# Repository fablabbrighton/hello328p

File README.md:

# Hello 328p!

**Hello 328p** is designed to be a 100% Arduino Uno-compatible board, that can be easily fabricated by students in a fablab. It uses the ATmega328P microcontroller and is very heavily based on [Daniele Ingrassia's Satshakit board](https://github.com/satshakit/satshakit), which also serves the same purpose. The main changes to this design are to provide a simpler way to connect things to the board through more convenient headers and labelling on the board itself.

Please read [Daniele's documentation](https://github.com/satshakit/satshakit) for full details on this board. These docs will only address the changes made.

## Background

I have spent a few months exploring different approaches to making your own Arduino-compatible board. My aim is to find (or design myself) a board that can be easily milled and stuffed by students, and then used in their own interactive projects. I also wanted to lern more about Arduino, the ATMega328p and board design in the process. 

You can read more about that here: [DIY Arduino docs](https://fablabbrighton.github.io/digital-fabrication-module/diy-arduino/)

After trying many boards is a starting point, I found Daniele's Satshakit design, which was well-documented, simple, and tested in a Fablab. I successfully made and programmed the board, but I found the header arrangement rather unhelpful.

In this photo, I'm using my FabISP to program a Satshakit. You can see that it involves a lot of jumper wires, and that there is no simple connection between the 3x2 pin ISP header on the programmer, and the relevant pins on the target board. 

Similarly, programming using an FTDI cable or breakout board (as in the photo above) involves a non-intuitive routing of pins from the programming cable (or board) to the target.

The upside of this approach is that the board design is very simple. Almost all the pins from the microcontroller are simply exposed out to pins on headers that surround it. The traces are very straightforward.

However, that pushes some complexity back onto the user, who has to figure out which pins to connect where, when burning the bootloader, or whenever they want to program the board. I think there is a friendlier way to do this, with only a small overhead in complexity of traces. _Hello 328p_ is my attempt at that.

The photo below shows the Hello 328p board being programmed with a FabISP, via one simple ribbon cable. You can also see the handy pads for connecting a power supply with crocodile clips.

## Hello 328p header layout

This diagram shows all the headers, and which pins on the chip they are connected to. In addition, pin functions for the FTDI and ISP headers are highlighted in pink, and the Arduino labels for analogue and digital pins are highlighted in yellow.

You may also wish to consult the official pinout for the ATmega328P chip (TQFP package) from the datasheet:

## Programming the board

Following the Satshakit instructions: 

> A satshakit board is **totally like an Arduino board**, thus is possible to use the Arduino IDE without any modification. When you finish solder satshakit, you're ready to program it. If you want to use satshakit as an Arduino, you first need to **upload Arduino bootloader**. This will also set the ATmega328P fuses as the same of an Arduino UNO.
> To do this you need to use a **programmer**, for example another Arduino or FabISP. If you plan to program a satshakit with an Arduino, be sure to upload the **Arduino as ISP skecth** before connecting the satshakit to it.

Where we diverge from the Satshakit process is that our connections are simpler. If you're using a FabISP, simply connect the ribbon cable to the ISP on both boards. the GND pin on the ISP heder is marked with a G.

To program with an FTDI cable, simply connect to the header labelled FTDI. Again, the GND pin is marked with a G.

Returning to the original instructions:

> Once everything is connected, follow these steps to upload Arduino bootloader:

> 1. open Arduino IDE
> 2. select proper programmer (for example Arduino as ISP or USBtinyISP)
> 3. select Arduino UNO as board
> 4. click on tools->Burn Bootloader

> With a satshakit cnc or satshakit laser you can use an **FTDI USB cable to upload and use you favourite sketch** without the need to use a programmer anymore.

> Remember that if you don't have an FTDI cable you always need a programmer, and to select **File->Upload using a programmer** to upload the code to satshakit.

License
--
This work is licensed under the terms of Attribution-NonCommercial-ShareAlike 4.0 International ([CC BY-NC-SA 4.0](https://creativecommons.org/licenses/by-nc-sa/4.0/)).

Disclaimer  
--

<div class="align-justify">
This hardware/software is provided "as is", and you use the hardware/software at your own risk. Under no circumstances shall any author be liable for direct, indirect, special, incidental, or consequential damages resulting from the use, misuse, or inability to use this hardware/software, even if the authors have been advised of the possibility of such damages.</div>

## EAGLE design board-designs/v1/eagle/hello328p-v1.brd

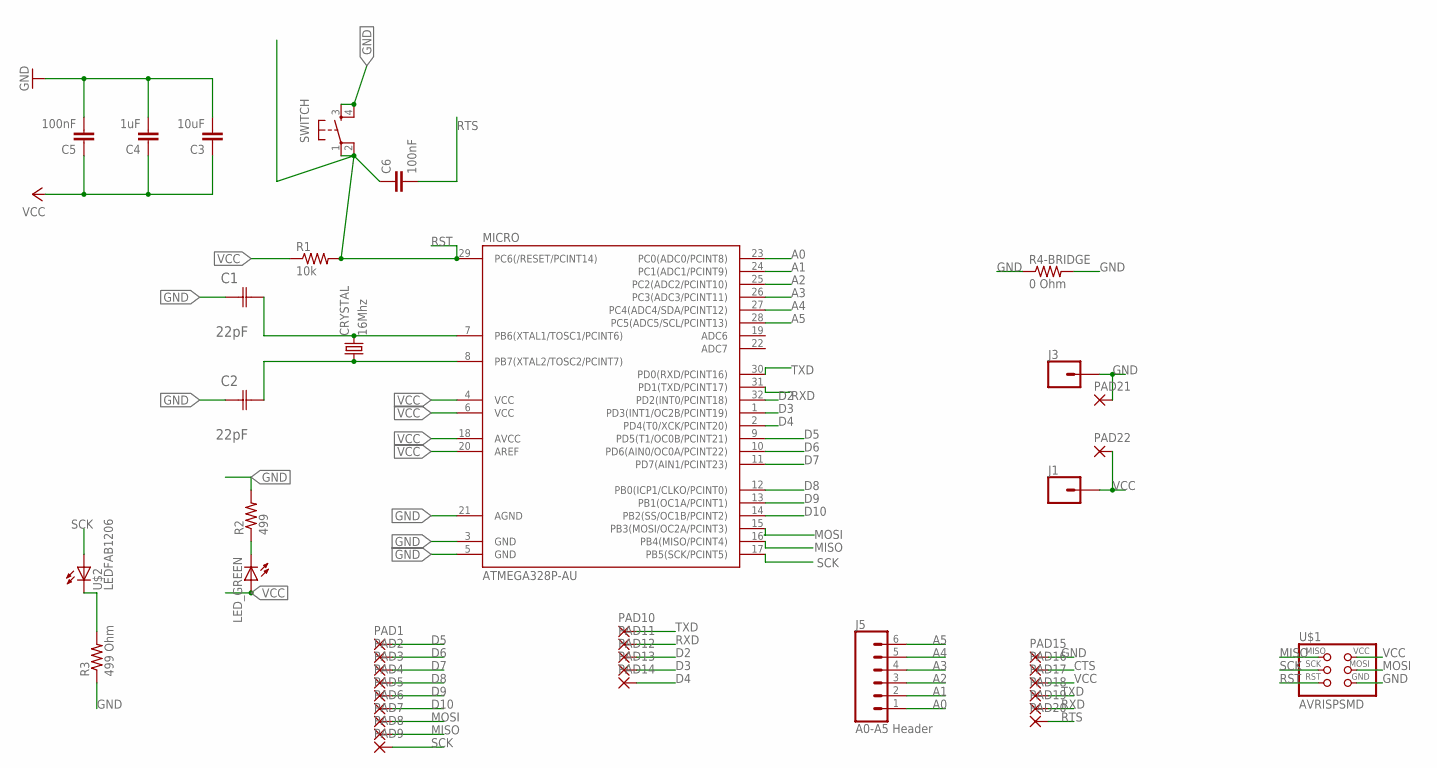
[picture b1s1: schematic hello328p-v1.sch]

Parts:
C1, C2: 22pF; CAPC3216X178N
C3: 10uF; 1206
C4: 1uF; 1206
C5, C6: 100nF; 1206
CRYSTAL: 16Mhz; CSM-7X-DU
J1, J3: CONN_01SNAP-MALE; SNAP-MALE
J5: A0-A5 Header; 1X06_SMD_MALE
LED_GREEN: LED1206; 1206
MICRO: ATMEGA328P-AU; TQFP32-08
PAD1, PAD2, PAD3, PAD4, PAD5, PAD6, PAD7, PAD8, PAD9, PAD10, PAD11, PAD12, PAD13, PAD14, PAD15, PAD16, PAD17, PAD18, PAD19, PAD20, PAD21, PAD22: SMD2; SMD1,27-2,54
R1: 10k; 1206
R2: 499; 1206
R3: 499 Ohm; R1206FAB
R4-BRIDGE: 0 Ohm; R1206FAB
SWITCH: 6MM_SWITCH6MM_SWITCH; 6MM_SWITCH
U$1: AVRISPSMD; 2X03SMD
U$2: LEDFAB1206; LED1206FAB

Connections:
A0: J5.1, MICRO.23 (PC0(ADC0/PCINT8))
A1: J5.2, MICRO.24 (PC1(ADC1/PCINT9))
A2: J5.3, MICRO.25 (PC2(ADC2/PCINT10))
A3: J5.4, MICRO.26 (PC3(ADC3/PCINT11))
A4: J5.5, MICRO.27 (PC4(ADC4/SDA/PCINT12))
A5: J5.6, MICRO.28 (PC5(ADC5/SCL/PCINT13))
CTS: PAD16.1
D2: MICRO.32 (PD2(INT0/PCINT18)), PAD12.1
D3: MICRO.1 (PD3(INT1/OC2B/PCINT19)), PAD13.1
D4: MICRO.2 (PD4(T0/XCK/PCINT20)), PAD14.1
D5: MICRO.9 (PD5(T1/OC0B/PCINT21)), PAD1.1
D6: MICRO.10 (PD6(AIN0/OC0A/PCINT22)), PAD2.1
D7: MICRO.11 (PD7(AIN1/PCINT23)), PAD3.1
D8: MICRO.12 (PB0(ICP1/CLKO/PCINT0)), PAD4.1
D9: MICRO.13 (PB1(OC1A/PCINT1)), PAD5.1
D10: MICRO.14 (PB2(SS/OC1B/PCINT2)), PAD6.1
GND: C1.1 (C1), C2.1 (C1), C3.2, C4.2, C5.2, J3.2, MICRO.3 (GND), MICRO.5 (GND), MICRO.21 (AGND), PAD15.1, PAD21.1, R2.2, R3.1, R4-BRIDGE.1, R4-BRIDGE.2, SWITCH.3 (S), SWITCH.4 (S1), U$1.6 (GND)
MISO: MICRO.16 (PB4(MISO/PCINT4)), PAD8.1, U$1.1 (MISO)
MOSI: MICRO.15 (PB3(MOSI/OC2A/PCINT3)), PAD7.1, U$1.4 (MOSI)
unnamed: R3.2, U$2.2 (C)
unnamed: C1.2 (C2), CRYSTAL.2, MICRO.7 (PB6(XTAL1/TOSC1/PCINT6))
unnamed: C2.2 (C2), CRYSTAL.1, MICRO.8 (PB7(XTAL2/TOSC2/PCINT7))
unnamed: LED_GREEN.2 (C), R2.1
RST: C6.1, MICRO.29 (PC6(/RESET/PCINT14)), R1.2, SWITCH.1, SWITCH.2 (P1), U$1.5 (RST)
RTS: C6.2, PAD20.1
RXD: MICRO.31 (PD1(TXD/PCINT17)), PAD11.1, PAD19.1
SCK: MICRO.17 (PB5(SCK/PCINT5)), PAD9.1, U$1.3 (SCK), U$2.1 (A)
TXD: MICRO.30 (PD0(RXD/PCINT16)), PAD10.1, PAD18.1
VCC: C3.1, C4.1, C5.1, J1.2, LED_GREEN.1 (A), MICRO.4 (VCC), MICRO.6 (VCC), MICRO.18 (AVCC), MICRO.20 (AREF), PAD17.1, PAD22.1, R1.1, U$1.2 (VCC)

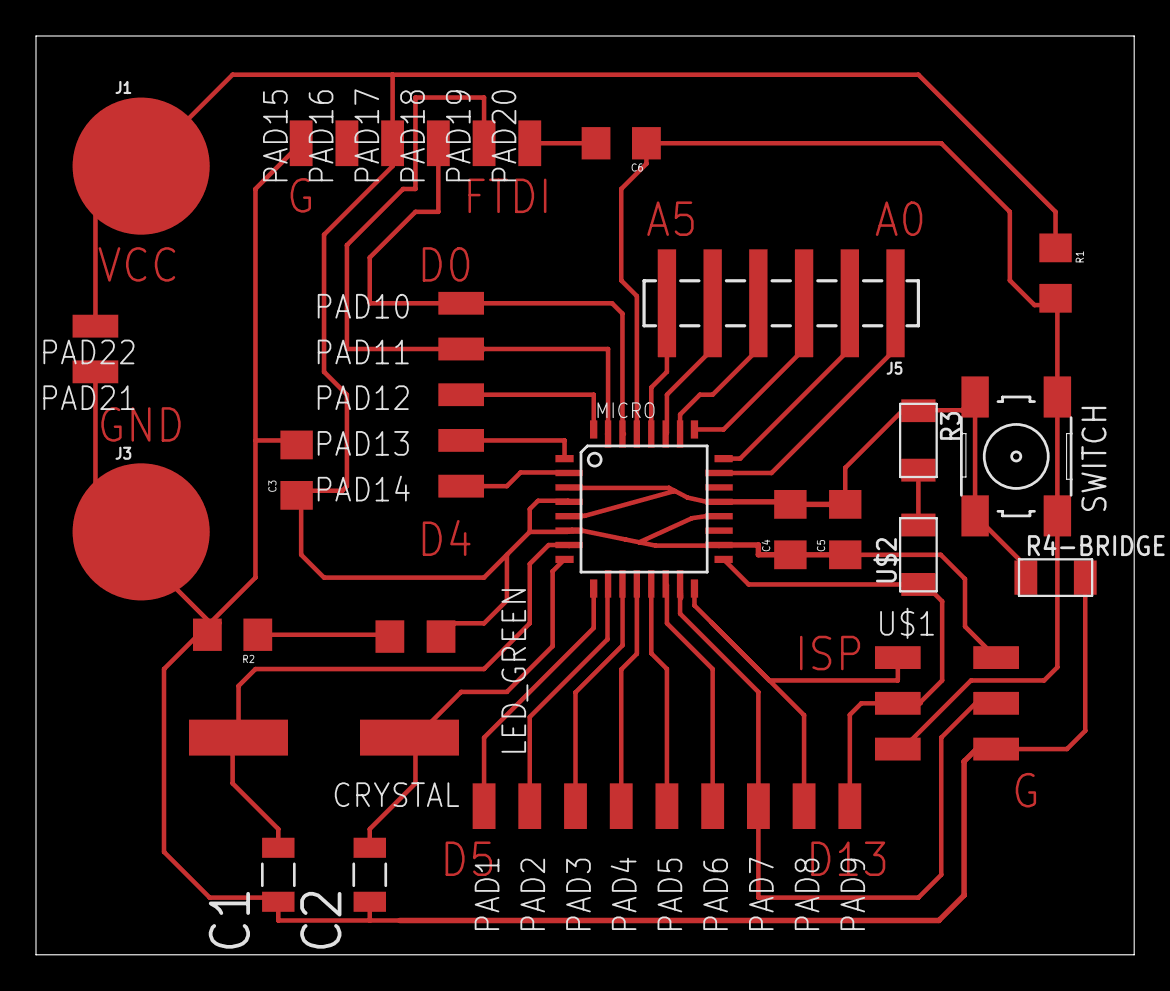
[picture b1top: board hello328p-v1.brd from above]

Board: 2 copper layers, 61.0 x 51.0 mm, 41 parts (0 on the bottom side), 28 nets.

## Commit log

2019-03-14 readme
2019-03-14 readme updates
2019-03-17 add board files
2019-03-18 pinout added

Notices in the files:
parts and their libraries:
01_SparkFun: Licensing: CC v3.0 Share-Alike You are welcome to use this library for commercial purposes.
SparkFun-Connectors: Licensing: Creative Commons ShareAlike 4.0 International - https://creativecommons.org/licenses/by-sa/4.0
